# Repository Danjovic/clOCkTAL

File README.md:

# clOCkTAL
Binary Coded Octal clock with auto brightness control, based on a PIC16F688

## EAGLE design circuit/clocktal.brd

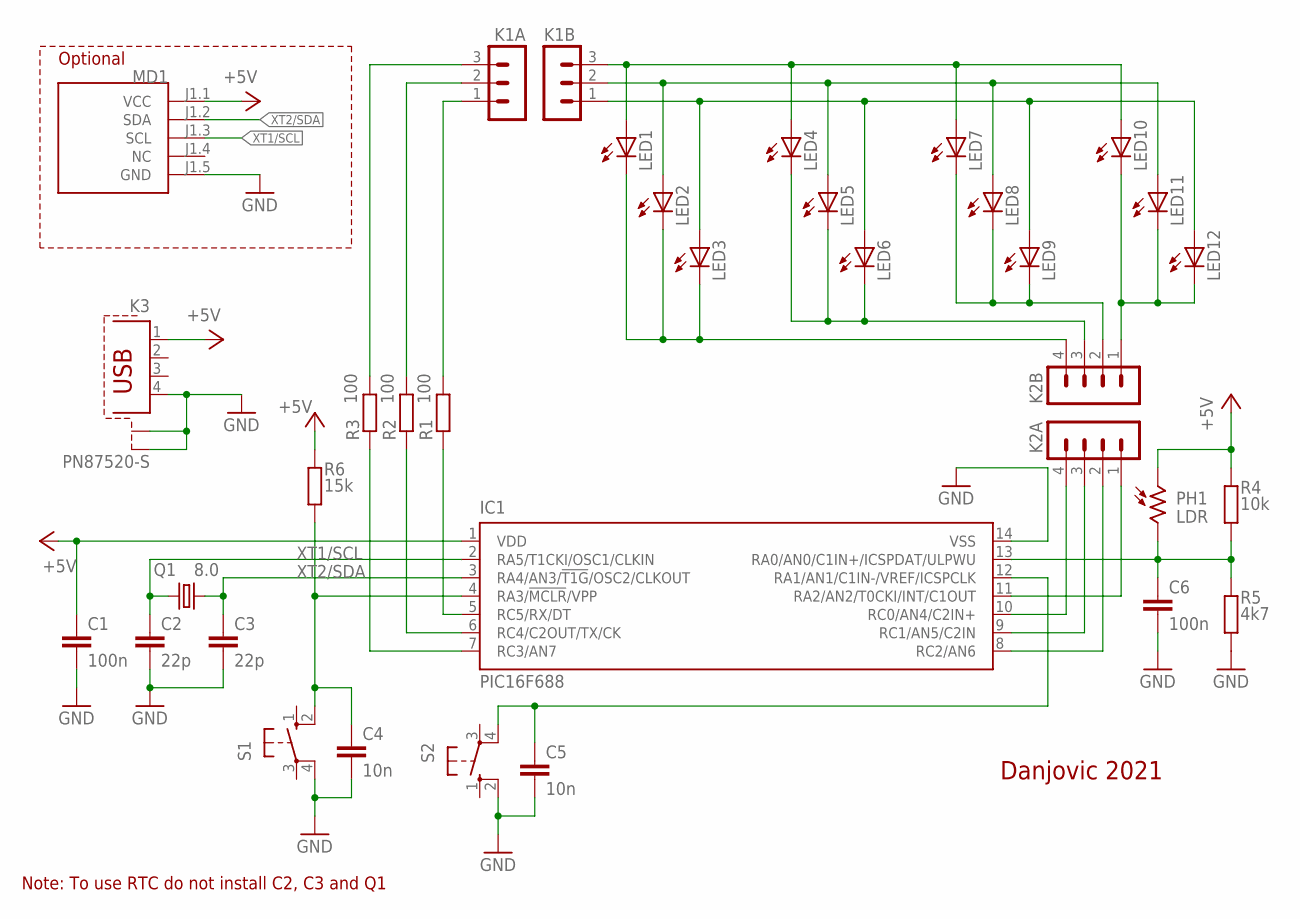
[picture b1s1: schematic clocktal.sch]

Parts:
C1, C6: 100n; C050-025X75L
C2, C3: 22p; C050-024X044L
C4, C5: 10n; C050-025X75L
IC1: PIC16F688; DIL14
K1A, K1B: MA03-1
K2A, K2B: MA04-1
K3: PN87520-S
LED1, LED2, LED3, LED4, LED5, LED6, LED7, LED8, LED9, LED10, LED11, LED12: LED3MM_L
MD1: RTC-DS3231_L; RTC-DS3231-SMALL_L
PH1: LDR; T0-46-A10XX
Q1: 8.0; HC49U-V
R1, R2, R3: 100; 0204/7L
R4: 10k; 0204/7L
R5: 4k7; 0204/7L
R6: 15k; 0204/7L
S1, S2: 10-XX; B3F-10XX

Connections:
+5V: C1.1, IC1.1 (VDD), K3.1, MD1.J1.1 (VCC), PH1.1, R4.1, R6.1
B0: K1B.1, LED3.A, LED6.A, LED9.A, LED12.A
B1: K1B.2, LED2.A, LED5.A, LED8.A, LED11.A
B2: K1B.3, LED1.A, LED4.A, LED7.A, LED10.A
BIT0: IC1.5 (RC5/RX/DT), R1.1
BIT0A: K1A.1, R1.2
BIT1: IC1.6 (RC4/C2OUT/TX/CK), R2.1
BIT1A: K1A.2, R2.2
BIT2: IC1.7 (RC3/AN7), R3.1
BIT2A: K1A.3, R3.2
BUTTON1: C4.1, IC1.4 (RA3/!MCLR!/VPP), R6.2, S1.2 (S1)
BUTTON2: C5.1, IC1.12 (RA1/AN1/C1IN-/VREF/ICSPCLK), S2.4 (P1)
DGT0: K2B.1, LED10.K (C), LED11.K (C), LED12.K (C)
DGT1: K2B.2, LED7.K (C), LED8.K (C), LED9.K (C)
DGT2: K2B.3, LED4.K (C), LED5.K (C), LED6.K (C)
DGT3: K2B.4, LED1.K (C), LED2.K (C), LED3.K (C)
DIGIT0: IC1.11 (RA2/AN2/T0CKI/INT/C1OUT), K2A.1
DIGIT1: IC1.8 (RC2/AN6), K2A.2
DIGIT2: IC1.9 (RC1/AN5/C2IN), K2A.3
DIGIT3: IC1.10 (RC0/AN4/C2IN+), K2A.4
GND: C1.2, C2.2, C3.2, C4.2, C5.2, C6.2, IC1.14 (VSS), K3.4, K3.S1, K3.S2, MD1.J1.5 (GND), R5.1, S1.4 (P1), S2.2 (S1)
LDR: C6.1, IC1.13 (RA0/AN0/C1IN+/ICSPDAT/ULPWU), PH1.2, R4.2, R5.2
XT1/SCL: C2.1, IC1.2 (RA5/T1CKI/OSC1/CLKIN), MD1.J1.3 (SCL), Q1.1
XT2/SDA: C3.1, IC1.3 (RA4/AN3/!T1G!/OSC2/CLKOUT), MD1.J1.2 (SDA), Q1.2

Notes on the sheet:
Danjovic 2021
Optional
Note: To use RTC do not install C2, C3 and Q1

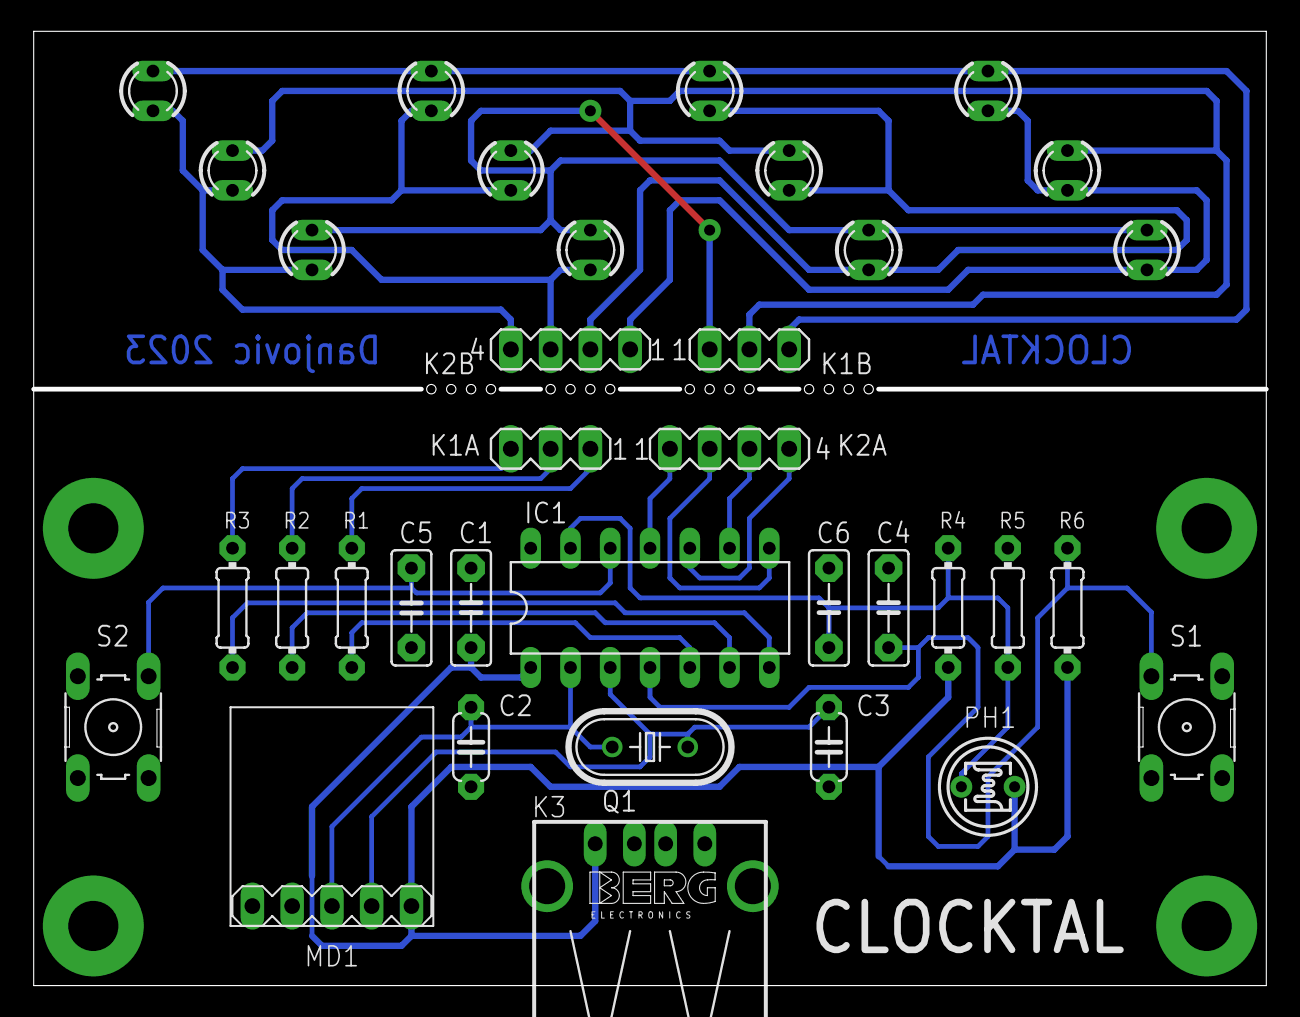
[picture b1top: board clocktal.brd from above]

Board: 2 copper layers, 78.7 x 61.0 mm, 35 parts (0 on the bottom side), 24 nets.

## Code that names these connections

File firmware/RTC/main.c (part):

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//                                            

// Button Stuff 
#define BUTTON1 RA3  // !RA3
#define BUTTON2 RA1  // !RA1
#define _tresholdTime 4  // 16ms * 4 ~65ms

// I2C Stuff
#define SDA  RA4
#define SCL  RA5
#define sendACK     true
#define sendNACK    false
#define RTC_ADDRESS 0x68
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       	// update display
        switch (digit) {
			case 0: // least significant digit;
			   RC0 = 1; // erase last display
			   if (minutes & (1<<0) ) RC5 = 1; else RC5 = 0;  
			   if (minutes & (1<<1) ) RC4 = 1; else RC4 = 0;  
			   if (minutes & (1<<2) ) RC3 = 1; else RC3 = 0;  
			   RA2 = 0; // Turn on this display
			   break;
			   
			case 1:
			   RA2 = 1; // erase last display
			   if (minutes & (1<<3) ) RC5 = 1; else RC5 = 0;  
			   if (minutes & (1<<4) ) RC4 = 1; else RC4 = 0;  
			   if (minutes & (1<<5) ) RC3 = 1; else RC3 = 0;
			   RC2 = 0; // Turn on this display        
			   break; 
		   
			case 2:
			   RC2 = 1; // erase last display
			   if (hours   & (1<<0) ) RC5 = 1; else RC5 = 0;  
			   if (hours   & (1<<1) ) RC4 = 1; else RC4 = 0;  
			   if (hours   & (1<<2) ) RC3 = 1; else RC3 = 0; 
			   RC1 = 0; // Turn on this display        
			   break;   
		 
			case 3:  // most significant digit
			   RC1 = 1; // erase last display
			   if (hours   & (1<<3) ) RC5 = 1; else RC5 = 0;  
			   if (hours   & (1<<4) ) RC4 = 1; else RC4 = 0;  
			   if (hours   & (1<<5) ) RC3 = 1; else RC3 = 0;  
			   RC0 = 0; // Turn on this display 
			   break;        
        } // end switch
        
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            go = 1;                        // main tick every 16.384 ms 
	    }
    } else if (tickCounter == tOFF ) {   // rudimentary PWM
       RA2=1;                            // Turns off all displays before
       RC2=1;                            // the next cycle
       RC1=1;
       RC0=1;
    }	
    
	T0IF = 0;
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
   // Initialize A/D converter
   ANSEL = (1<<0); // Configure analog/digital I/O (ANSEL)
   ADCON0 = 0b00000000; // CHS[2..0] = 000 -> Channel AN0 (@pin RA0)
   ADCON1 = 0b01110000;	 //  ADCS1 [2..0] = x11 -> FRC Internal 500KHz oscillator
   ADON = 1;
   GO_NOT_DONE = 1;   // Set GO/DONE bit to start conversions
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
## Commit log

2021-08-29 Basic Release
2023-05-16 Added version with DS3231 RTC module support
2023-05-16 Cleanup, reorganization of directories
2023-05-17 added Single Sided PCB design
2023-05-17 Improved PCB aesthetics
2023-05-17 Added rendered images of PCB
2023-05-26 Bug fixes

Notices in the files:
firmware/RTC/main.c:
Release under GPL V2.0
